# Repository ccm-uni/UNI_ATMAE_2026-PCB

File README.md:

# UNI ATMAE 2026 PCB Design

https://lastminuteengineers.com/esp32-pinout-reference/

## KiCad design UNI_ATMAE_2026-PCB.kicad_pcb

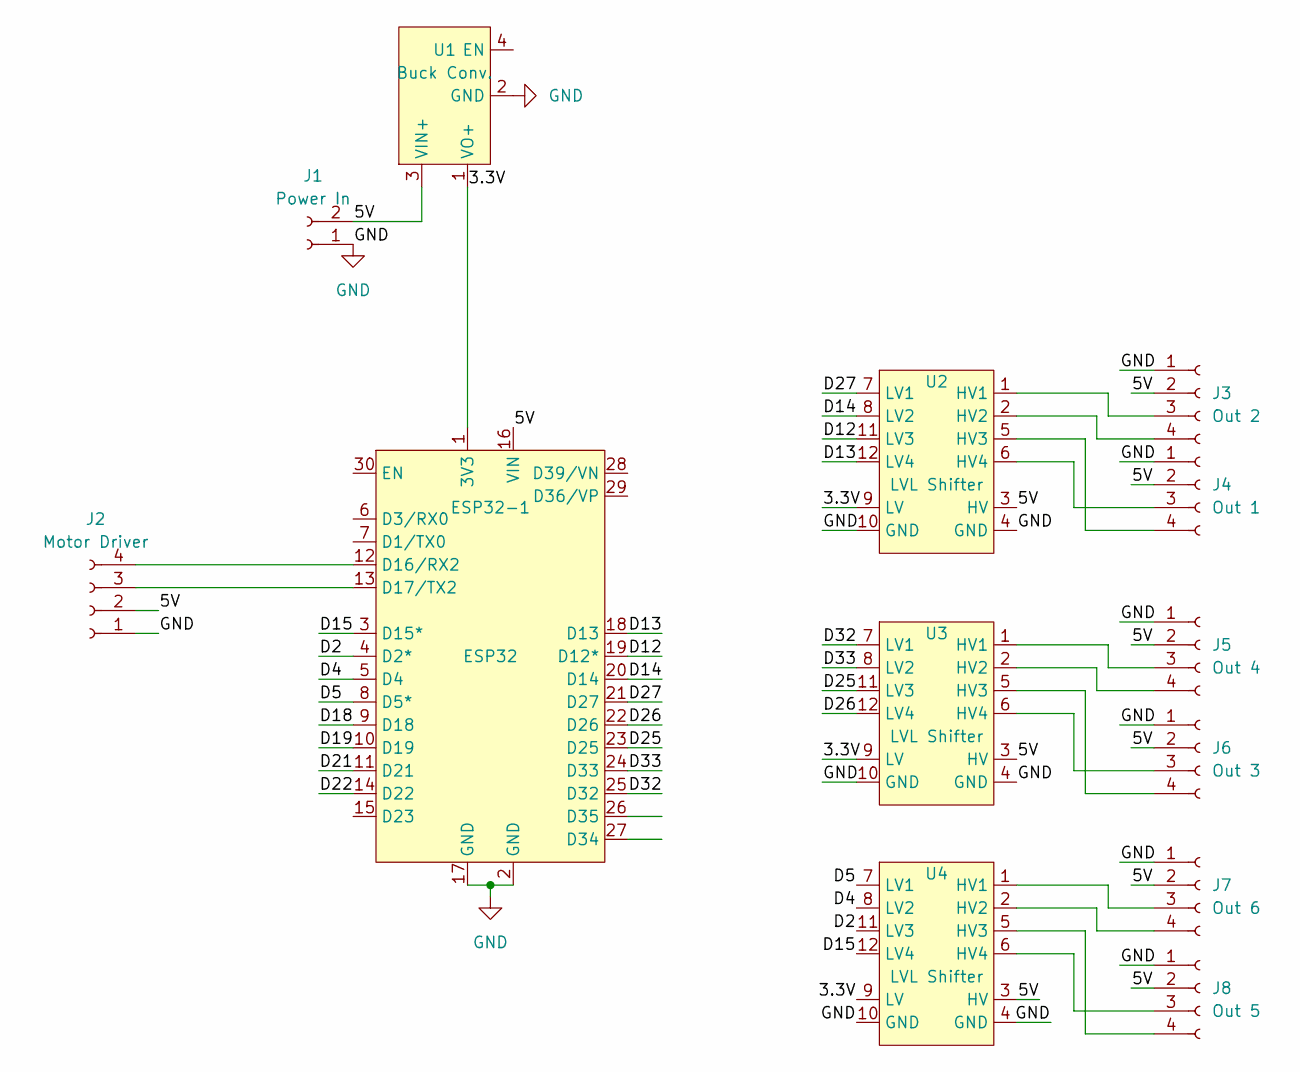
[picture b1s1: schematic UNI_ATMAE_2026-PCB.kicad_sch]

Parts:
ESP32-1: ESP32; ESP32_DevBoard
J1: Power In; JST_XH_B2B-XH-A_1x02_P2.50mm_Vertical
J2: Motor Driver; JST_XH_B4B-XH-A_1x04_P2.50mm_Vertical
J3: Out 2; JST_XH_B4B-XH-A_1x04_P2.50mm_Vertical
J4: Out 1; JST_XH_B4B-XH-A_1x04_P2.50mm_Vertical
J5: Out 4; JST_XH_B4B-XH-A_1x04_P2.50mm_Vertical
J6: Out 3; JST_XH_B4B-XH-A_1x04_P2.50mm_Vertical
J7: Out 6; JST_XH_B4B-XH-A_1x04_P2.50mm_Vertical
J8: Out 5; JST_XH_B4B-XH-A_1x04_P2.50mm_Vertical
U1: Buck Conv.; Voltage Buck conv. (DROK)
U2, U3, U4: LVL Shifter; Logic Level Shifter-4Ch

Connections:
/3.3V: ESP32-1.1 (3V3), U1.1 (VO+), U2.9 (LV), U3.9 (LV), U4.9 (LV)
/5V: ESP32-1.16 (VIN), J1.2, J2.2, J3.2, J4.2, J5.2, J6.2, J7.2, J8.2, U1.3 (VIN+), U2.3 (HV), U3.3 (HV), U4.3 (HV)
/D2: ESP32-1.4 (D2*), U4.11 (LV3)
/D4: ESP32-1.5 (D4), U4.8 (LV2)
/D5: ESP32-1.8 (D5*), U4.7 (LV1)
/D12: ESP32-1.19 (D12*), U2.11 (LV3)
/D13: ESP32-1.18 (D13), U2.12 (LV4)
/D14: ESP32-1.20 (D14), U2.8 (LV2)
/D15: ESP32-1.3 (D15*), U4.12 (LV4)
/D18: ESP32-1.9 (D18)
/D19: ESP32-1.10 (D19)
/D21: ESP32-1.11 (D21)
/D22: ESP32-1.14 (D22)
/D25: ESP32-1.23 (D25), U3.11 (LV3)
/D26: ESP32-1.22 (D26), U3.12 (LV4)
/D27: ESP32-1.21 (D27), U2.7 (LV1)
/D32: ESP32-1.25 (D32), U3.7 (LV1)
/D33: ESP32-1.24 (D33), U3.8 (LV2)
GND: ESP32-1.2 (GND), ESP32-1.17 (GND), J1.1, J2.1, J3.1, J4.1, J5.1, J6.1, J7.1, J8.1, U1.2 (GND), U2.4 (GND), U2.10 (GND), U3.4 (GND), U3.10 (GND), U4.4 (GND), U4.10 (GND)
unnamed: ESP32-1.12 (D16/RX2), J2.4
unnamed: ESP32-1.13 (D17/TX2), J2.3
unnamed: J3.3, U2.1 (HV1)
unnamed: J3.4, U2.2 (HV2)
unnamed: J4.3, U2.6 (HV4)
unnamed: J4.4, U2.5 (HV3)
unnamed: J5.3, U3.1 (HV1)
unnamed: J5.4, U3.2 (HV2)
unnamed: J6.3, U3.6 (HV4)
unnamed: J6.4, U3.5 (HV3)
unnamed: J7.3, U4.1 (HV1)
unnamed: J7.4, U4.2 (HV2)
unnamed: J8.3, U4.6 (HV4)
unnamed: J8.4, U4.5 (HV3)

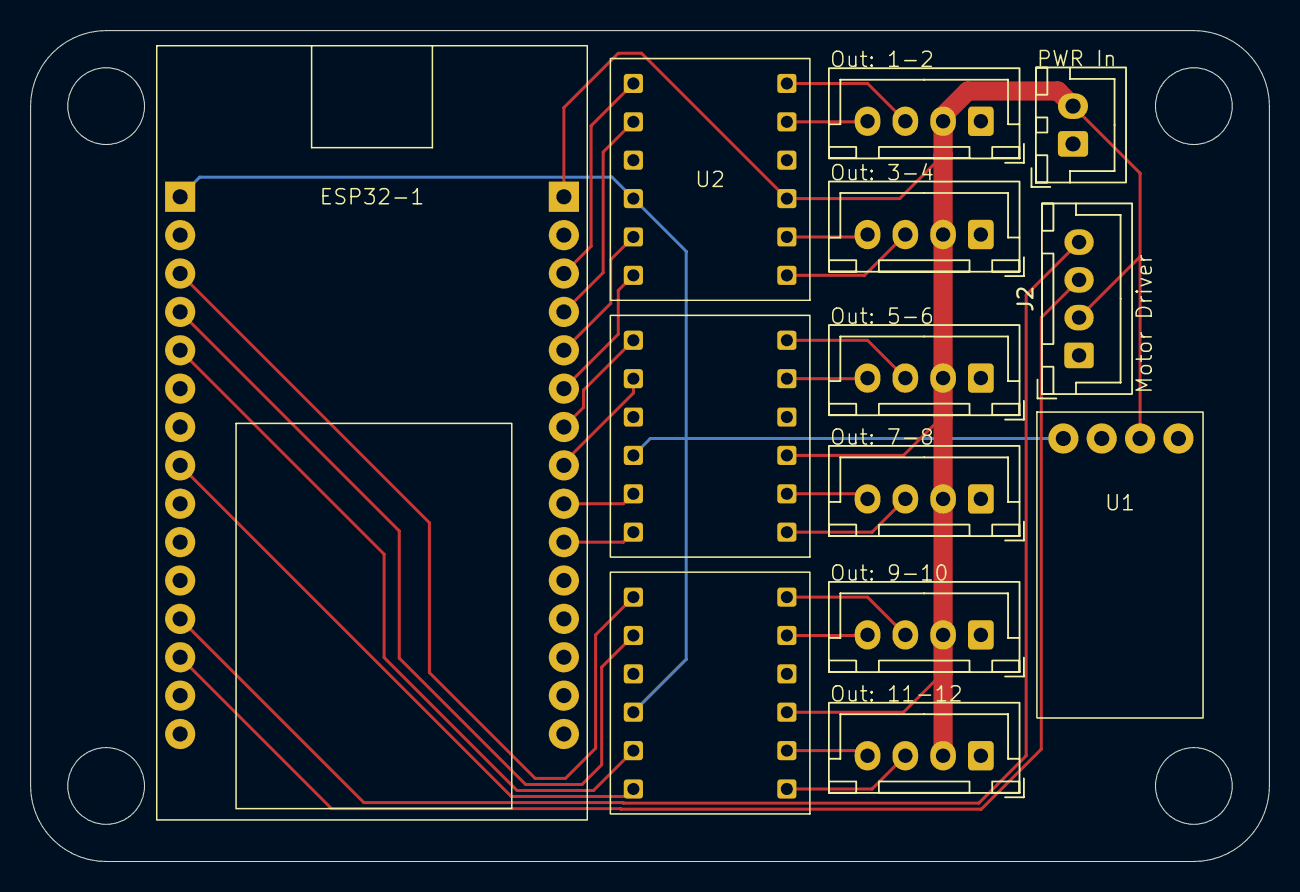
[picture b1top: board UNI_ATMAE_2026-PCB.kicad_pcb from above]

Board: 2 copper layers, 82.0 x 55.0 mm, 13 parts (0 on the bottom side), 29 nets.
